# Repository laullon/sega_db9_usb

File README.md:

# Sega DB9 to USB - Arduino Leonardo ( atmega32u4 )

## Photos

## Schematics

## Other Schematics

### Arduino Pro Mini

### ATmega32U4

### SEGA DB9

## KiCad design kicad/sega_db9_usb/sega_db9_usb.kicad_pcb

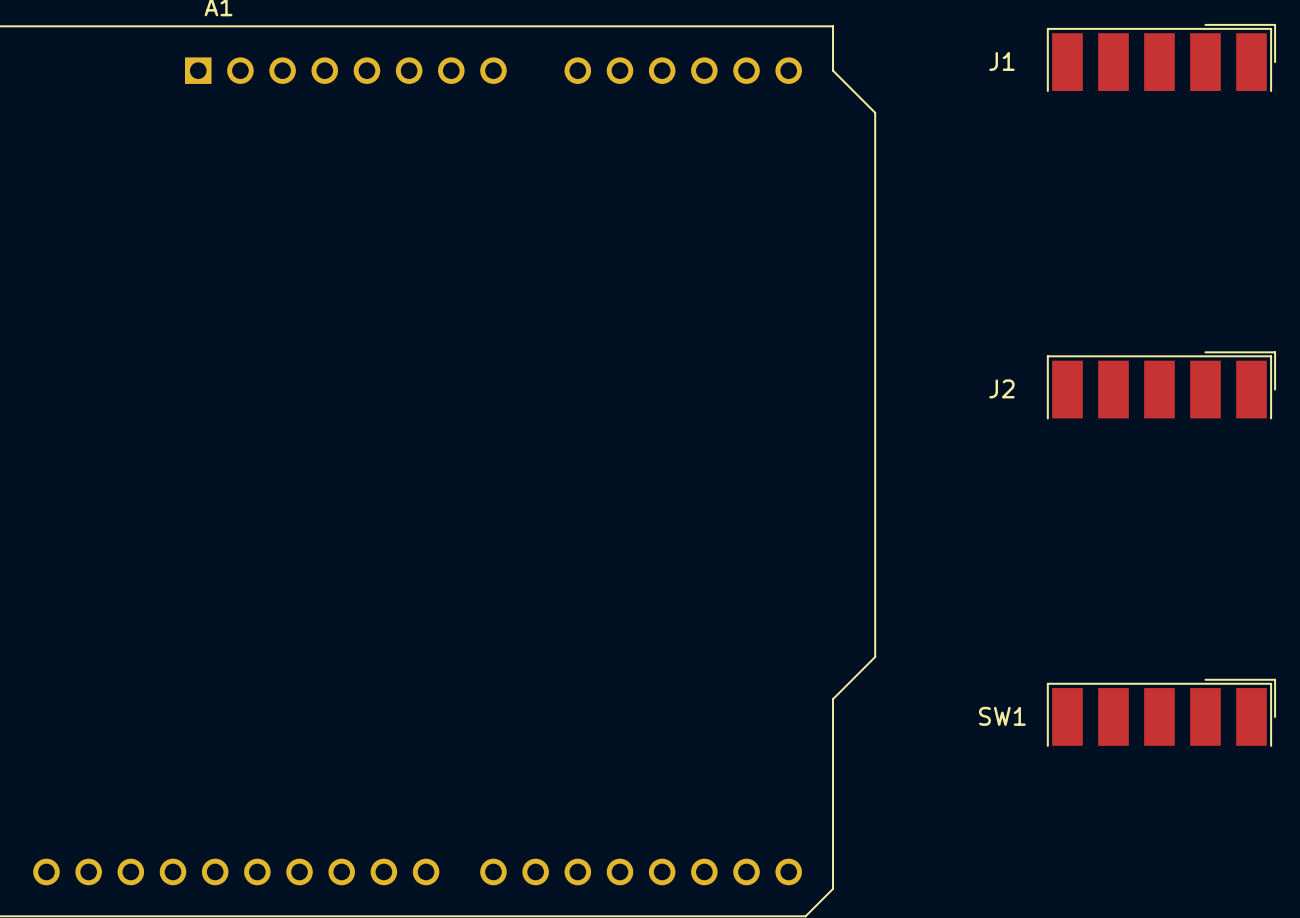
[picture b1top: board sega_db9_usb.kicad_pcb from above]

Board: 2 copper layers, 4 parts (0 on the bottom side), 16 nets, no tracks yet.

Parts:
A1: Arduino_Leonardo_micro; Arduino_UNO_R3
J1: Player 1; DSUB-9_Female_EdgeMount_P2.77mm
J2: Player 2; DSUB-9_Female_EdgeMount_P2.77mm
SW1: Select; DSUB-9_Female_EdgeMount_P2.77mm

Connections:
/Select: A1.16 (D15/SLCK), J1.7, J2.7
GND: A1.4 (GND), J1.8, J2.8, SW1.1
unnamed: A1.1 (D1/TX), SW1.2
unnamed: A1.5 (D2/SDA), J1.1
unnamed: A1.6 (D3/SCL), J1.2
unnamed: A1.7 (D4), J1.3
unnamed: A1.8 (D5), J1.4
unnamed: A1.11 (D8), J1.6
unnamed: A1.12 (D9), J1.9
unnamed: A1.13 (D10), J2.9
unnamed: A1.14 (D16/M0SI), J2.6
unnamed: A1.17 (D18), J2.4
unnamed: A1.18 (D19), J2.3
unnamed: A1.19 (D20), J2.2
unnamed: A1.20 (D21), J2.1
VCC: A1.21 (VCC), J1.5, J2.5

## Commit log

2022-03-28 inital version
2022-03-28 cleanup
2022-03-29 kicad
2022-03-30 bug pins 8 and 7
2022-03-30 Wroking
2022-04-07 2 players
